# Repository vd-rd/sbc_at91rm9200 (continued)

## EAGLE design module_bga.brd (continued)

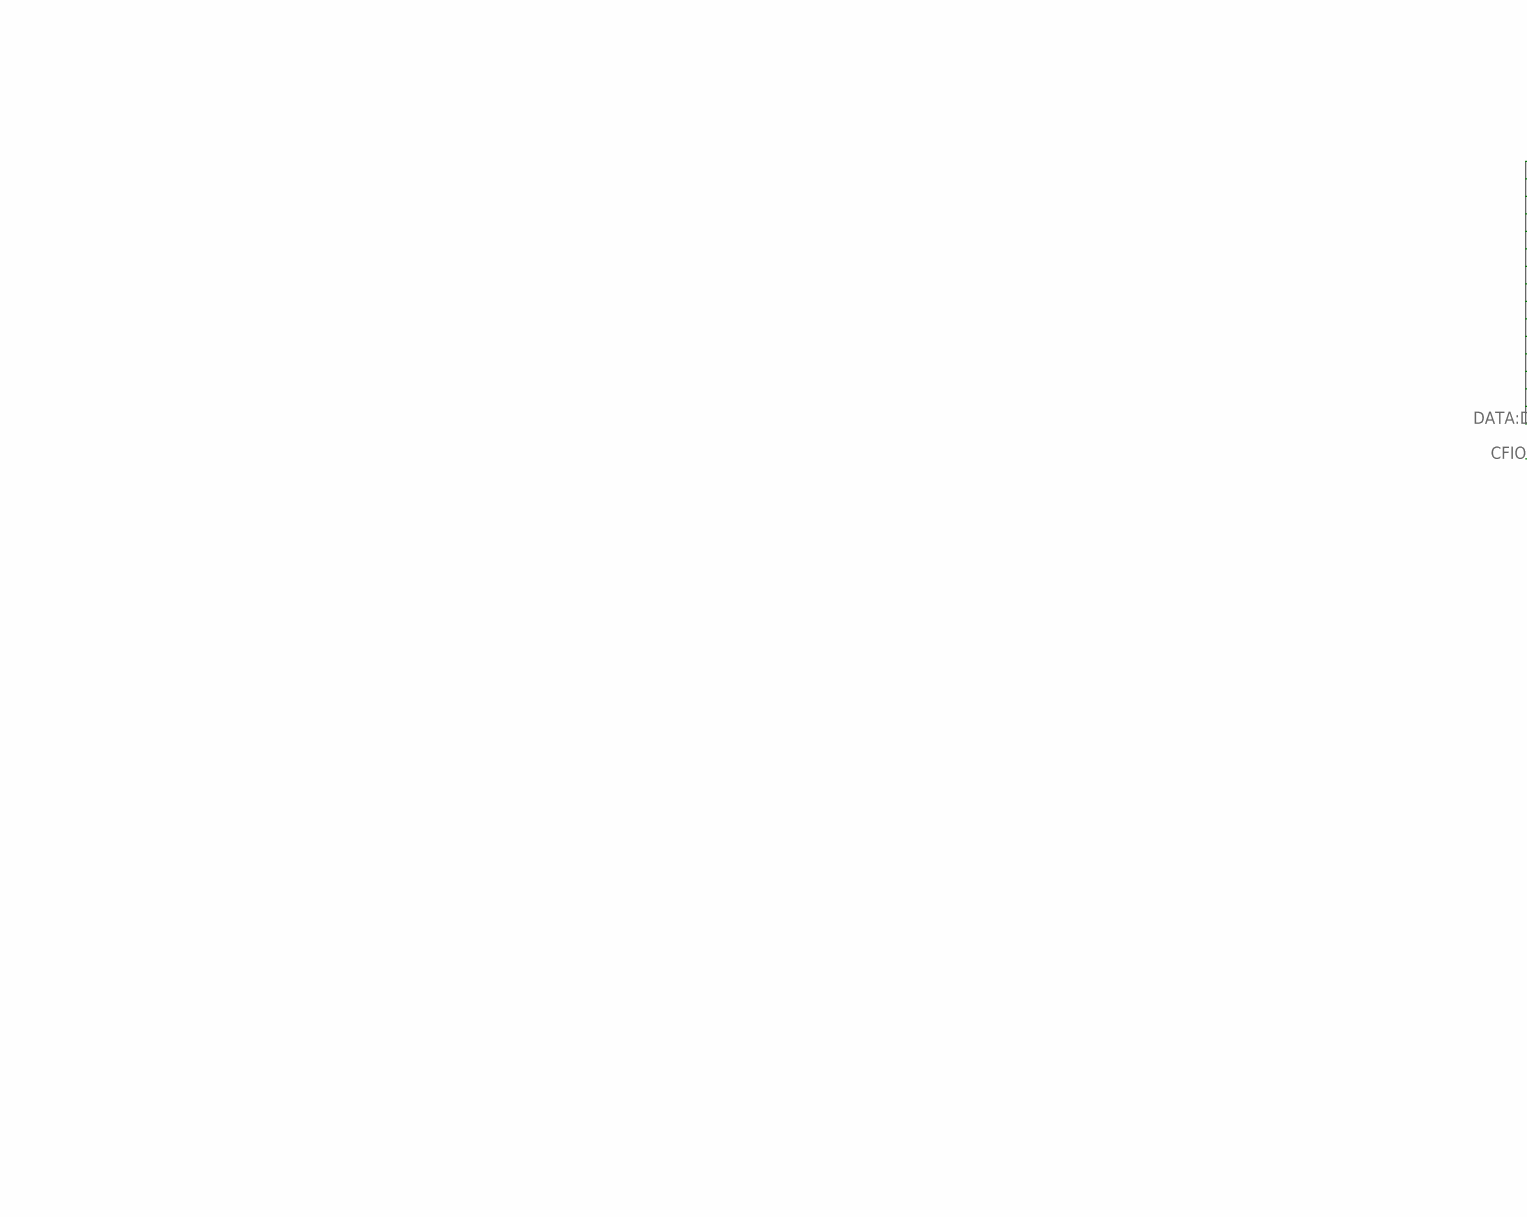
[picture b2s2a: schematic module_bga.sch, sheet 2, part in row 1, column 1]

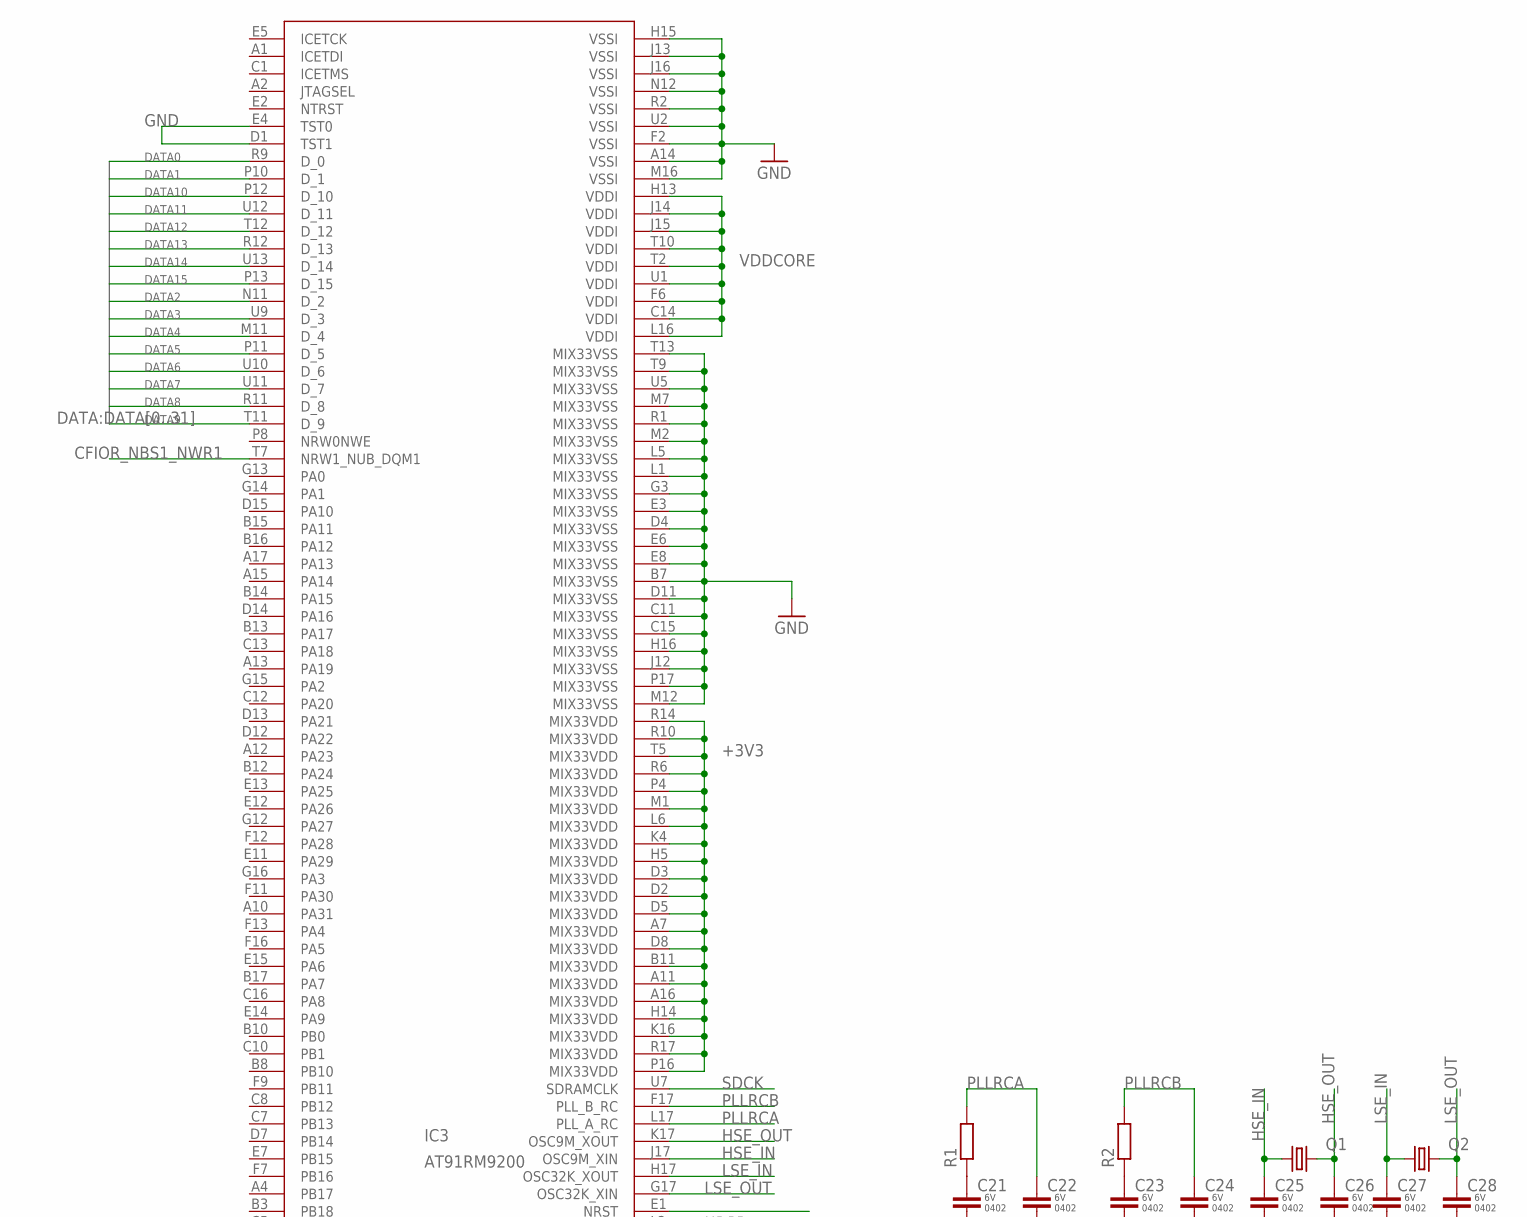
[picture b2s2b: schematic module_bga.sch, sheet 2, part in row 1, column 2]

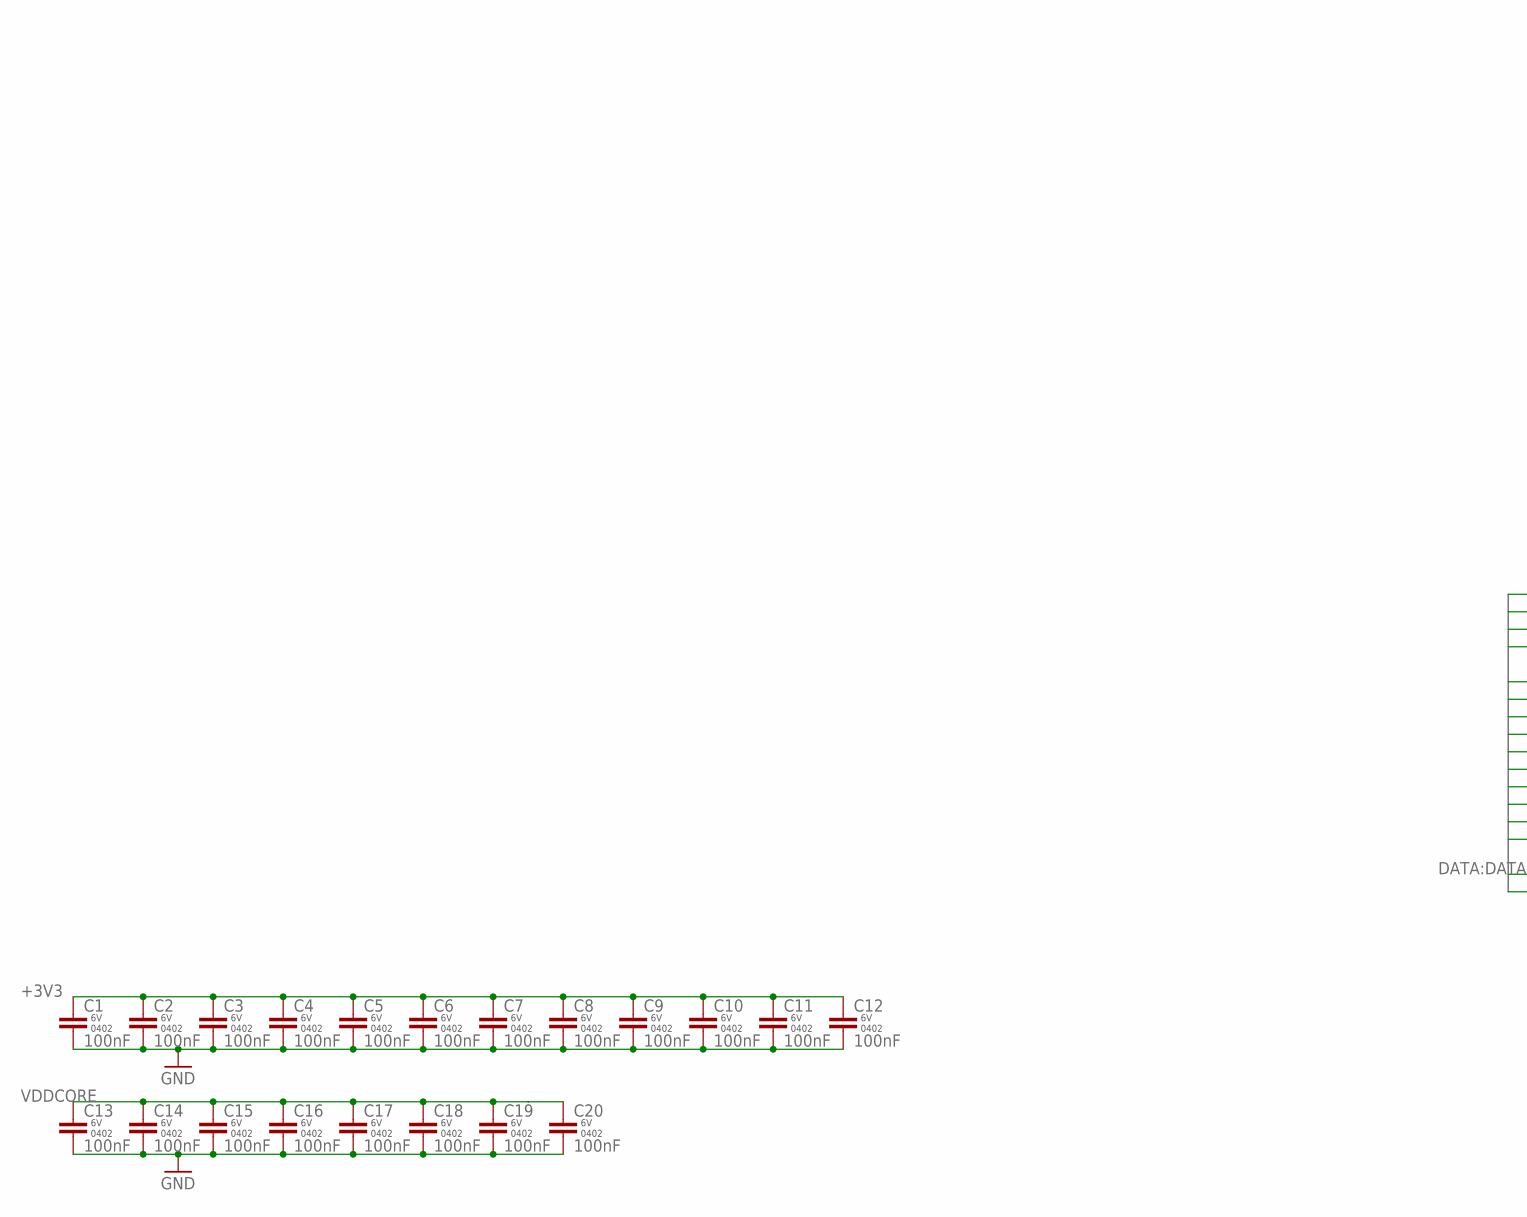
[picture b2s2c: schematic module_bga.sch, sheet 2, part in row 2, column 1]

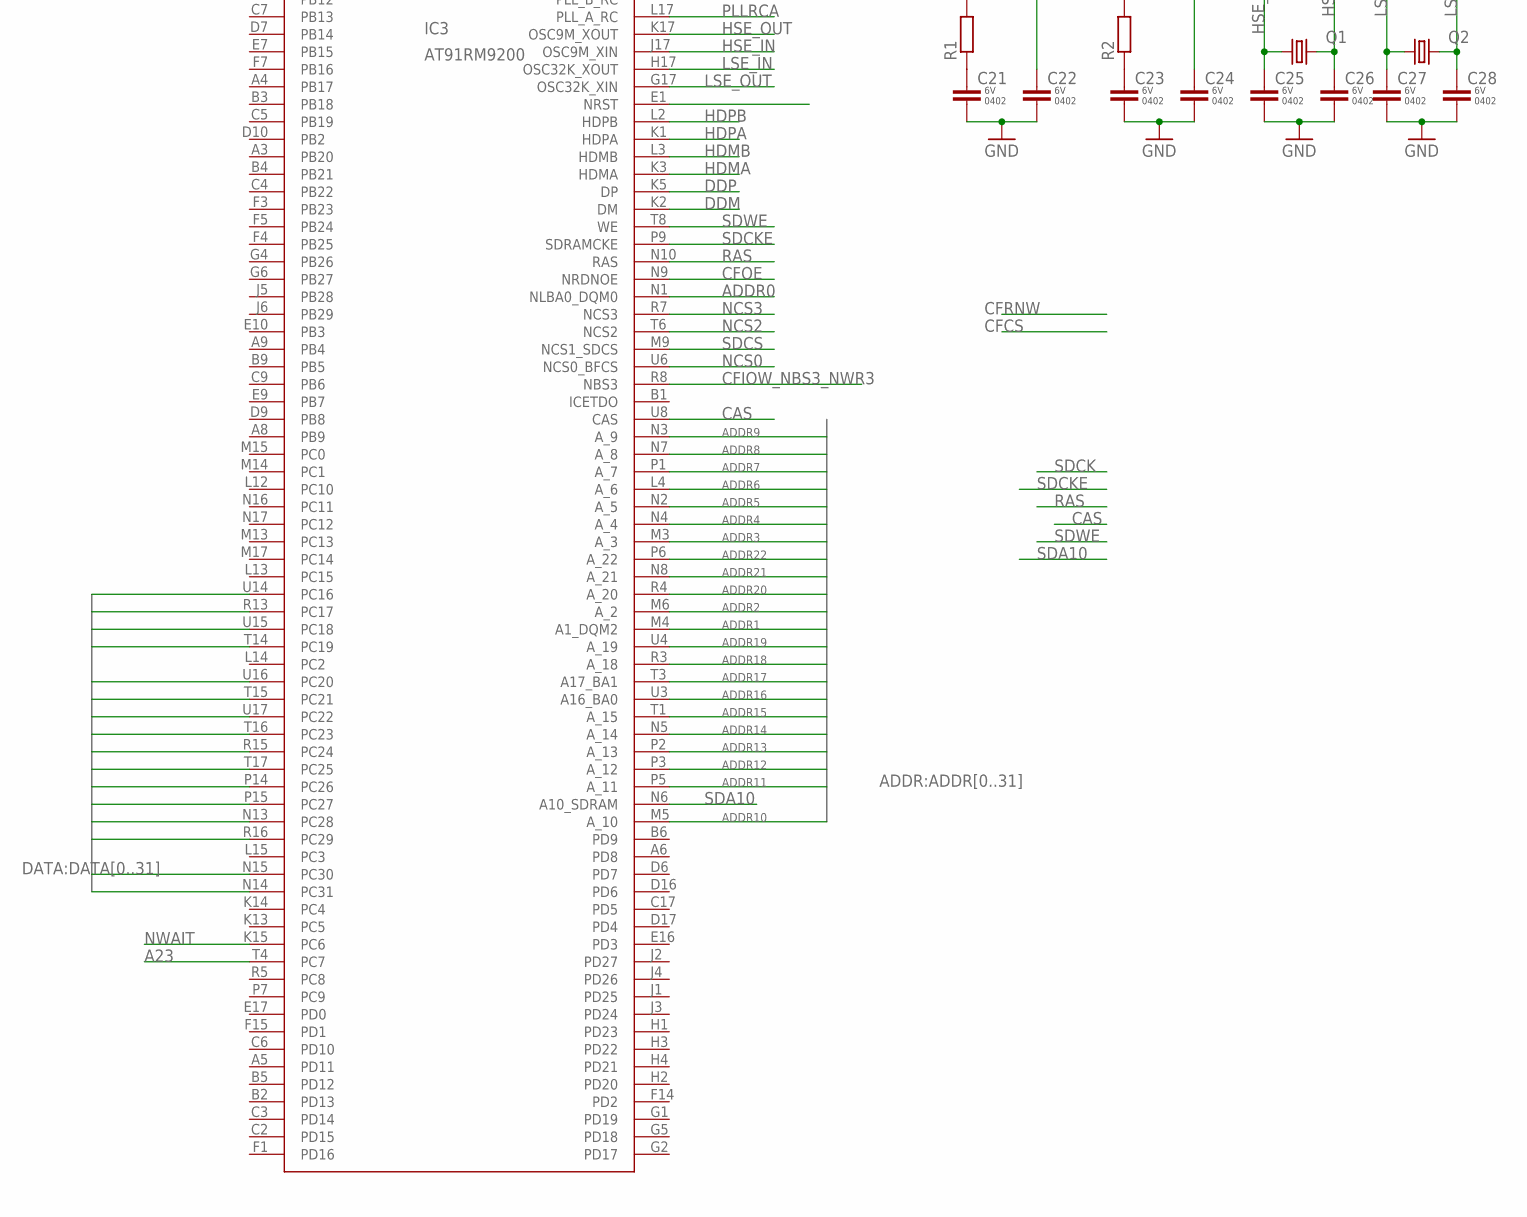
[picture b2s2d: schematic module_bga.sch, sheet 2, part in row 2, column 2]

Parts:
C1, C2, C3, C4, C5, C6, C7, C8, C9, C10, C11, C12, C13, C14, C15, C16, C17, C18, C19, C20: 100nF; C0402K
C21, C22, C23, C24, C25, C26, C27, C28: CAP-0402; C0402K
IC3: AT91RM9200; LFBGA256_A_291X326
Q1: KX-7; 3.2X2.5_KX-7
Q2: KX-327-NHF; 3.2X1.5
R1, R2: R-EU_R0402; R0402

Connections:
+3V3: C1.1, C2.1, C3.1, C4.1, C5.1, C6.1, C7.1, C8.1, C9.1, C10.1, C11.1, C12.1, IC3.A7 (MIX33VDD), IC3.A11 (MIX33VDD), IC3.A16 (MIX33VDD), IC3.B11 (MIX33VDD), IC3.D2 (MIX33VDD), IC3.D3 (MIX33VDD), IC3.D5 (MIX33VDD), IC3.D8 (MIX33VDD), IC3.H5 (MIX33VDD), IC3.H14 (MIX33VDD), IC3.K4 (MIX33VDD), IC3.K16 (MIX33VDD), IC3.L6 (MIX33VDD), IC3.M1 (MIX33VDD), IC3.P4 (MIX33VDD), IC3.P16 (MIX33VDD), IC3.R6 (MIX33VDD), IC3.R10 (MIX33VDD), IC3.R14 (MIX33VDD), IC3.R17 (MIX33VDD), IC3.T5 (MIX33VDD); also elsewhere on the board
A23: IC3.T4 (PC7)
ADDR0: IC3.N1 (NLBA0_DQM0); also elsewhere on the board
ADDR1: IC3.M4 (A1_DQM2); also elsewhere on the board
ADDR2: IC3.M6 (A_2); also elsewhere on the board
ADDR3: IC3.M3 (A_3); also elsewhere on the board
ADDR4: IC3.N4 (A_4); also elsewhere on the board
ADDR5: IC3.N2 (A_5); also elsewhere on the board
ADDR6: IC3.L4 (A_6); also elsewhere on the board
ADDR7: IC3.P1 (A_7); also elsewhere on the board
ADDR8: IC3.N7 (A_8); also elsewhere on the board
ADDR9: IC3.N3 (A_9); also elsewhere on the board
ADDR10: IC3.M5 (A_10); also elsewhere on the board
ADDR11: IC3.P5 (A_11); also elsewhere on the board
ADDR12: IC3.P3 (A_12)
ADDR13: IC3.P2 (A_13); also elsewhere on the board
ADDR14: IC3.N5 (A_14); also elsewhere on the board
ADDR15: IC3.T1 (A_15)
ADDR16: IC3.U3 (A16_BA0); also elsewhere on the board
ADDR17: IC3.T3 (A17_BA1); also elsewhere on the board
ADDR18: IC3.R3 (A_18)
ADDR19: IC3.U4 (A_19)
ADDR20: IC3.R4 (A_20)
ADDR21: IC3.N8 (A_21)
ADDR22: IC3.P6 (A_22)
CAS: IC3.U8 (CAS); also elsewhere on the board
CFIOR_NBS1_NWR1: IC3.T7 (NRW1_NUB_DQM1); also elsewhere on the board
CFIOW_NBS3_NWR3: IC3.R8 (NBS3); also elsewhere on the board
CFOE: IC3.N9 (NRDNOE)
DATA0: IC3.R9 (D_0); also elsewhere on the board
DATA1: IC3.P10 (D_1); also elsewhere on the board
DATA2: IC3.N11 (D_2); also elsewhere on the board
DATA3: IC3.U9 (D_3); also elsewhere on the board
DATA4: IC3.M11 (D_4); also elsewhere on the board
DATA5: IC3.P11 (D_5); also elsewhere on the board
DATA6: IC3.U10 (D_6); also elsewhere on the board
DATA7: IC3.U11 (D_7); also elsewhere on the board
DATA8: IC3.R11 (D_8); also elsewhere on the board
DATA9: IC3.T11 (D_9); also elsewhere on the board
DATA10: IC3.P12 (D_10); also elsewhere on the board
DATA11: IC3.U12 (D_11); also elsewhere on the board
DATA12: IC3.T12 (D_12); also elsewhere on the board
DATA13: IC3.R12 (D_13); also elsewhere on the board
DATA14: IC3.U13 (D_14); also elsewhere on the board
DATA15: IC3.P13 (D_15); also elsewhere on the board
DATA16: IC3.U14 (PC16); also elsewhere on the board
DATA17: IC3.R13 (PC17); also elsewhere on the board
DATA18: IC3.U15 (PC18); also elsewhere on the board
DATA19: IC3.T14 (PC19); also elsewhere on the board
DATA20: IC3.U16 (PC20); also elsewhere on the board
DATA21: IC3.T15 (PC21); also elsewhere on the board
DATA22: IC3.U17 (PC22); also elsewhere on the board
DATA23: IC3.T16 (PC23); also elsewhere on the board
DATA24: IC3.R15 (PC24); also elsewhere on the board
DATA25: IC3.T17 (PC25); also elsewhere on the board
DATA26: IC3.P14 (PC26); also elsewhere on the board
DATA27: IC3.P15 (PC27); also elsewhere on the board
DATA28: IC3.N13 (PC28); also elsewhere on the board
DATA29: IC3.R16 (PC29); also elsewhere on the board
DATA30: IC3.N15 (PC30); also elsewhere on the board
DATA31: IC3.N14 (PC31); also elsewhere on the board
DDM: IC3.K2 (DM)
DDP: IC3.K5 (DP)
GND: C1.2, C2.2, C3.2, C4.2, C5.2, C6.2, C7.2, C8.2, C9.2, C10.2, C11.2, C12.2, C13.2, C14.2, C15.2, C16.2, C17.2, C18.2, C19.2, C20.2, C21.2, C22.2, C23.2, C24.2, C25.2, C26.2, C27.2, C28.2, IC3.A14 (VSSI), IC3.B7 (MIX33VSS), IC3.C11 (MIX33VSS), IC3.C15 (MIX33VSS), IC3.D1 (TST1), IC3.D4 (MIX33VSS), IC3.D11 (MIX33VSS), IC3.E3 (MIX33VSS), IC3.E4 (TST0), IC3.E6 (MIX33VSS), IC3.E8 (MIX33VSS), IC3.F2 (VSSI), IC3.G3 (MIX33VSS), IC3.H15 (VSSI), IC3.H16 (MIX33VSS), IC3.J12 (MIX33VSS), IC3.J13 (VSSI), IC3.J16 (VSSI), IC3.L1 (MIX33VSS), IC3.L5 (MIX33VSS), IC3.M2 (MIX33VSS), IC3.M7 (MIX33VSS), IC3.M12 (MIX33VSS), IC3.M16 (VSSI), IC3.N12 (VSSI), IC3.P17 (MIX33VSS), IC3.R1 (MIX33VSS), IC3.R2 (VSSI), IC3.T9 (MIX33VSS), IC3.T13 (MIX33VSS), IC3.U2 (VSSI), IC3.U5 (MIX33VSS); also elsewhere on the board
HDMA: IC3.K3 (HDMA)
HDMB: IC3.L3 (HDMB)
HDPA: IC3.K1 (HDPA)
HDPB: IC3.L2 (HDPB)
HSE_IN: C25.1, IC3.J17 (OSC9M_XIN), Q1.1
HSE_OUT: C26.1, IC3.K17 (OSC9M_XOUT), Q1.3 (2)
LSE_IN: C27.1, IC3.H17 (OSC32K_XOUT), Q2.1
LSE_OUT: C28.1, IC3.G17 (OSC32K_XIN), Q2.2
unnamed: C21.1, R1.1
unnamed: C23.1, R2.1
NCS0: IC3.U6 (NCS0_BFCS)
NCS2: IC3.T6 (NCS2)
NCS3: IC3.R7 (NCS3)
NWAIT: IC3.K15 (PC6)
PLLRCA: C22.1, IC3.L17 (PLL_A_RC), R1.2
PLLRCB: C24.1, IC3.F17 (PLL_B_RC), R2.2
RAS: IC3.N10 (RAS); also elsewhere on the board
SDA10: IC3.N6 (A10_SDRAM); also elsewhere on the board
SDCK: IC3.U7 (SDRAMCLK); also elsewhere on the board
SDCKE: IC3.P9 (SDRAMCKE); also elsewhere on the board
SDCS: IC3.M9 (NCS1_SDCS); also elsewhere on the board
SDWE: IC3.T8 (WE); also elsewhere on the board
VDDCORE: C13.1, C14.1, C15.1, C16.1, C17.1, C18.1, C19.1, C20.1, IC3.C14 (VDDI), IC3.F6 (VDDI), IC3.H13 (VDDI), IC3.J14 (VDDI), IC3.J15 (VDDI), IC3.L16 (VDDI), IC3.T2 (VDDI), IC3.T10 (VDDI), IC3.U1 (VDDI)

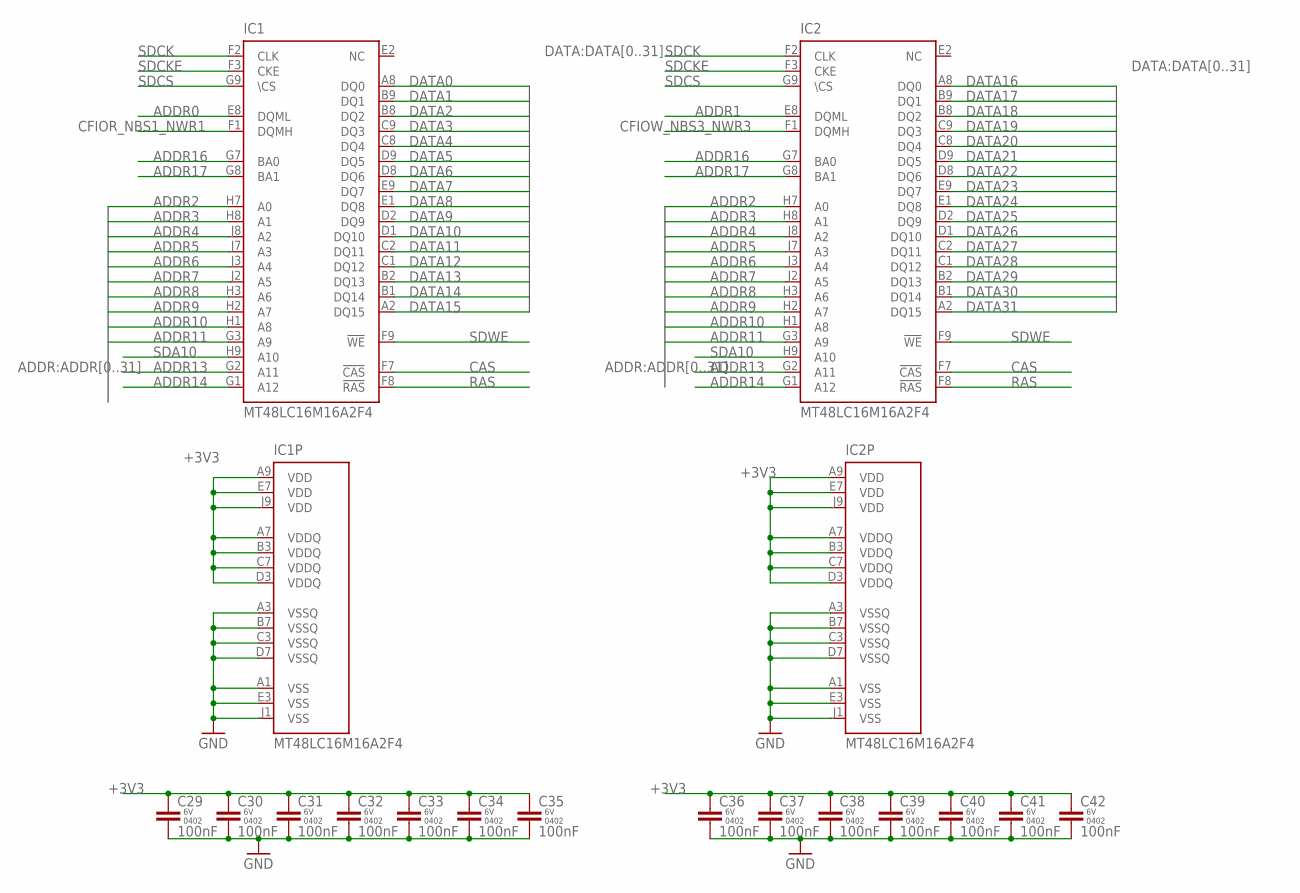
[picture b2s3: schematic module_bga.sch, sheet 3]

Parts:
C29, C30, C31, C32, C33, C34, C35, C36, C37, C38, C39, C40, C41, C42: 100nF; C0402K
IC1, IC2: MT48LC16M16A2F4; BGA81C80P9X9_800X800X100

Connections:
+3V3: C29.1, C30.1, C31.1, C32.1, C33.1, C34.1, C35.1, C36.1, C37.1, C38.1, C39.1, C40.1, C41.1, C42.1, IC1.A7 (VDDQ), IC1.A9 (VDD), IC1.B3 (VDDQ), IC1.C7 (VDDQ), IC1.D3 (VDDQ), IC1.E7 (VDD), IC1.J9 (VDD), IC2.A7 (VDDQ), IC2.A9 (VDD), IC2.B3 (VDDQ), IC2.C7 (VDDQ), IC2.D3 (VDDQ), IC2.E7 (VDD), IC2.J9 (VDD); also elsewhere on the board
ADDR0: IC1.E8 (DQML); also elsewhere on the board
ADDR1: IC2.E8 (DQML); also elsewhere on the board
ADDR2: IC1.H7 (A0), IC2.H7 (A0); also elsewhere on the board
ADDR3: IC1.H8 (A1), IC2.H8 (A1); also elsewhere on the board
ADDR4: IC1.J8 (A2), IC2.J8 (A2); also elsewhere on the board
ADDR5: IC1.J7 (A3), IC2.J7 (A3); also elsewhere on the board
ADDR6: IC1.J3 (A4), IC2.J3 (A4); also elsewhere on the board
ADDR7: IC1.J2 (A5), IC2.J2 (A5); also elsewhere on the board
ADDR8: IC1.H3 (A6), IC2.H3 (A6); also elsewhere on the board
ADDR9: IC1.H2 (A7), IC2.H2 (A7); also elsewhere on the board
ADDR10: IC1.H1 (A8), IC2.H1 (A8); also elsewhere on the board
ADDR11: IC1.G3 (A9), IC2.G3 (A9); also elsewhere on the board
ADDR13: IC1.G2 (A11), IC2.G2 (A11); also elsewhere on the board
ADDR14: IC1.G1 (A12), IC2.G1 (A12); also elsewhere on the board
ADDR16: IC1.G7 (BA0), IC2.G7 (BA0); also elsewhere on the board
ADDR17: IC1.G8 (BA1), IC2.G8 (BA1); also elsewhere on the board
CAS: IC1.F7 (!CAS), IC2.F7 (!CAS); also elsewhere on the board
CFIOR_NBS1_NWR1: IC1.F1 (DQMH); also elsewhere on the board
CFIOW_NBS3_NWR3: IC2.F1 (DQMH); also elsewhere on the board
DATA0: IC1.A8 (DQ0); also elsewhere on the board
DATA1: IC1.B9 (DQ1); also elsewhere on the board
DATA2: IC1.B8 (DQ2); also elsewhere on the board
DATA3: IC1.C9 (DQ3); also elsewhere on the board
DATA4: IC1.C8 (DQ4); also elsewhere on the board
DATA5: IC1.D9 (DQ5); also elsewhere on the board
DATA6: IC1.D8 (DQ6); also elsewhere on the board
DATA7: IC1.E9 (DQ7); also elsewhere on the board
DATA8: IC1.E1 (DQ8); also elsewhere on the board
DATA9: IC1.D2 (DQ9); also elsewhere on the board
DATA10: IC1.D1 (DQ10); also elsewhere on the board
DATA11: IC1.C2 (DQ11); also elsewhere on the board
DATA12: IC1.C1 (DQ12); also elsewhere on the board
DATA13: IC1.B2 (DQ13); also elsewhere on the board
DATA14: IC1.B1 (DQ14); also elsewhere on the board
DATA15: IC1.A2 (DQ15); also elsewhere on the board
DATA16: IC2.A8 (DQ0); also elsewhere on the board
DATA17: IC2.B9 (DQ1); also elsewhere on the board
DATA18: IC2.B8 (DQ2); also elsewhere on the board
DATA19: IC2.C9 (DQ3); also elsewhere on the board
DATA20: IC2.C8 (DQ4); also elsewhere on the board
DATA21: IC2.D9 (DQ5); also elsewhere on the board
DATA22: IC2.D8 (DQ6); also elsewhere on the board
DATA23: IC2.E9 (DQ7); also elsewhere on the board
DATA24: IC2.E1 (DQ8); also elsewhere on the board
DATA25: IC2.D2 (DQ9); also elsewhere on the board
DATA26: IC2.D1 (DQ10); also elsewhere on the board
DATA27: IC2.C2 (DQ11); also elsewhere on the board
DATA28: IC2.C1 (DQ12); also elsewhere on the board
DATA29: IC2.B2 (DQ13); also elsewhere on the board
DATA30: IC2.B1 (DQ14); also elsewhere on the board
DATA31: IC2.A2 (DQ15); also elsewhere on the board
GND: C29.2, C30.2, C31.2, C32.2, C33.2, C34.2, C35.2, C36.2, C37.2, C38.2, C39.2, C40.2, C41.2, C42.2, IC1.A1 (VSS), IC1.A3 (VSSQ), IC1.B7 (VSSQ), IC1.C3 (VSSQ), IC1.D7 (VSSQ), IC1.E3 (VSS), IC1.J1 (VSS), IC2.A1 (VSS), IC2.A3 (VSSQ), IC2.B7 (VSSQ), IC2.C3 (VSSQ), IC2.D7 (VSSQ), IC2.E3 (VSS), IC2.J1 (VSS); also elsewhere on the board
RAS: IC1.F8 (!RAS), IC2.F8 (!RAS); also elsewhere on the board
SDA10: IC1.H9 (A10), IC2.H9 (A10); also elsewhere on the board
SDCK: IC1.F2 (CLK), IC2.F2 (CLK); also elsewhere on the board
SDCKE: IC1.F3 (CKE), IC2.F3 (CKE); also elsewhere on the board
SDCS: IC1.G9 (\CS), IC2.G9 (\CS); also elsewhere on the board
SDWE: IC1.F9 (!WE), IC2.F9 (!WE); also elsewhere on the board

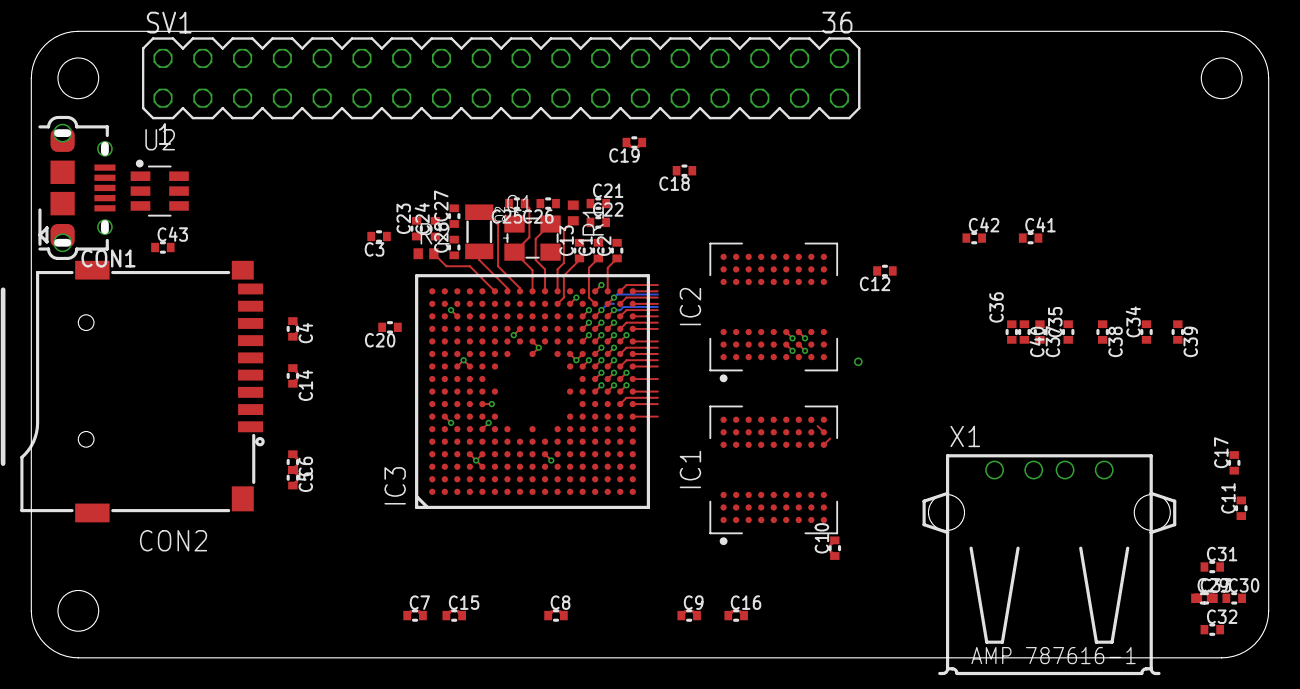
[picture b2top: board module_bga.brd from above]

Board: 4 copper layers, 79.0 x 40.0 mm, 55 parts (0 on the bottom side), 68 nets.

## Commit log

2019-04-08 repo bringup
2019-04-08 added documents
2019-04-08 added gitignore
2019-04-08 defined major connections
2019-04-09 added connectors
2019-04-09 added bga variant
2019-04-10 added bga sdram
2019-04-10 finished sdram routing
2019-04-11 updated schematic
2019-04-12 small fixes
2019-04-12 deleted extra files
2019-04-12 updated gitignore
2019-04-12 defined pinout
2019-04-12 refined board shape
2019-04-14 added power stages
2019-04-15 updated footprint positions
2019-04-15 added usb connections
2019-04-15 added power plane
2019-04-17 added documentation
2019-04-17 another board example
2019-04-19 board: bms pull-up for proper boot
2019-04-19 board: update render
2019-04-19 board: remove bga variant
2019-04-19 board: add i2c pullup
2019-04-21 board: define usb host connector interface
2019-04-21 schematic: define usb host nets
2019-04-21 layout: preliminary usb routing
2019-04-22 board: add missing pwr supply pin
2019-04-22 board: removed button
2019-04-22 schematic: added gpio connections
2019-04-22 board: rmii connector 1st draft
2019-04-24 layout: updated connectors
2019-04-24 layout: trace routing and optimisation
2019-04-24 schematic: defined led connections
2019-04-24 board: added missing pull-up for dataflash
2019-04-24 layout: initial rmii routing
2019-04-25 board: verified agains schematic checklist
2019-04-25 layout: clear routing errors
2019-04-25 layout: optimised descriptor placement
2019-04-25 layout: fixed dataflash footprint
2019-04-25 layout: added pinout descriptors
2019-04-25 board: added fiducials
2019-04-25 layout: fanout main connector
2019-04-25 added manual selection for power source
2019-04-25 layout: various traces routed'
2019-04-25 layout: defined usb support components
2019-04-25 layout: signal routing
2019-04-26 layout: small fixes
2019-04-26 board: exported bom
2019-05-03 schematic: added values for step-down
2019-05-07 finished board rev1
2019-05-10 project: updated documentation
2019-05-10 project: small fixes
2019-05-10 board: added testpoints
2019-05-10 board: matched JLC7628 stackup
